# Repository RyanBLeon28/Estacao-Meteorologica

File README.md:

<h1>Estação Meteorológica Microcontrolada</h1>

<div align="center">
    
</div>

As estações meteorológicas são equipamentos utilizados para monitoramento e registro de condições climáticas por meio de sensores que analisam parâmetros atmosféricos como temperatura, umidade, pressão, velocidade e direção do vento. Neste projeto, os sensores estão conectados a um microcontrolador responsável por realizar a leitura dos dados. Esses dados são enviados automaticamente por protocolo LoRa(Long Range) para um servidor remoto (Datalogger), que realiza o armazenamento e processamento das informações.

O sistema foi projetado para operar continuamente e com baixo consumo de energia, sendo ideal para aplicações em ambientes externos. A visualização dos dados é feita por meio de dashboards acessíveis via navegador, possibilitando o acompanhamento em tempo real das variáveis monitoradas.

<h2>Tecnologias Utilizadas</h2>

<ul>
    <li><strong>MQTT (Eclipse Mosquitto):</strong> protocolo leve de comunicação utilizado para transmitir os dados dos sensores de forma eficiente e confiável.</li>
    <li><strong>Node.js:</strong> ambiente de execução utilizado no backend para processar as mensagens recebidas e integrá-las aos demais componentes do sistema.</li>
    <li><strong>Node-RED:</strong> ferramenta baseada em fluxo que facilita a criação de integrações entre os dados do MQTT e os bancos de dados utilizados.</li>
    <li><strong>InfluxDB:</strong> banco de dados especializado em séries temporais, utilizado para armazenar os dados dos sensores com alta performance.</li>
    <li><strong>Grafana:</strong> plataforma para visualização de dados que permite criar dashboards interativos e intuitivos para o acompanhamento das variáveis climáticas.</li>
</ul>

<h2>Detalhamento do projeto</h2>

<p>Para mais detalhes sobre o desenvolvimento da estação, incluindo a calibração de sensores como o anemômetro e a integração dos dados, consulte o <a href="Estação_Meteorológica_Microcontrolada.pdf" target="_blank">Relatório Descritivo do Projeto</a>.</p>

<h2>Referências</h2>

<p>
NODE.JS. Node.js. Disponível em: <a href="https://nodejs.org/en">https://nodejs.org/en</a>. Acesso em: 19 maio 2023.
</p>
<p>
MOSQUITTO. Mosquitto. Disponível em: <a href="https://mosquitto.org/">https://mosquitto.org/</a>. Acesso em: 19 maio 2023.
</p>
<p>
NODE-RED. Node-RED. Disponível em: <a href="https://nodered.org/">https://nodered.org/</a>. Acesso em: 19 maio 2023.
</p>
<p>
INFLUXDATA. Documentation. Disponível em: <a href="https://docs.influxdata.com/">https://docs.influxdata.com/</a>. Acesso em: 19 maio 2023.
</p>
<p>
GRAFANA LABS. Grafana. Disponível em: <a href="https://grafana.com/">https://grafana.com/</a>. Acesso em: 19 maio 2023.
</p>

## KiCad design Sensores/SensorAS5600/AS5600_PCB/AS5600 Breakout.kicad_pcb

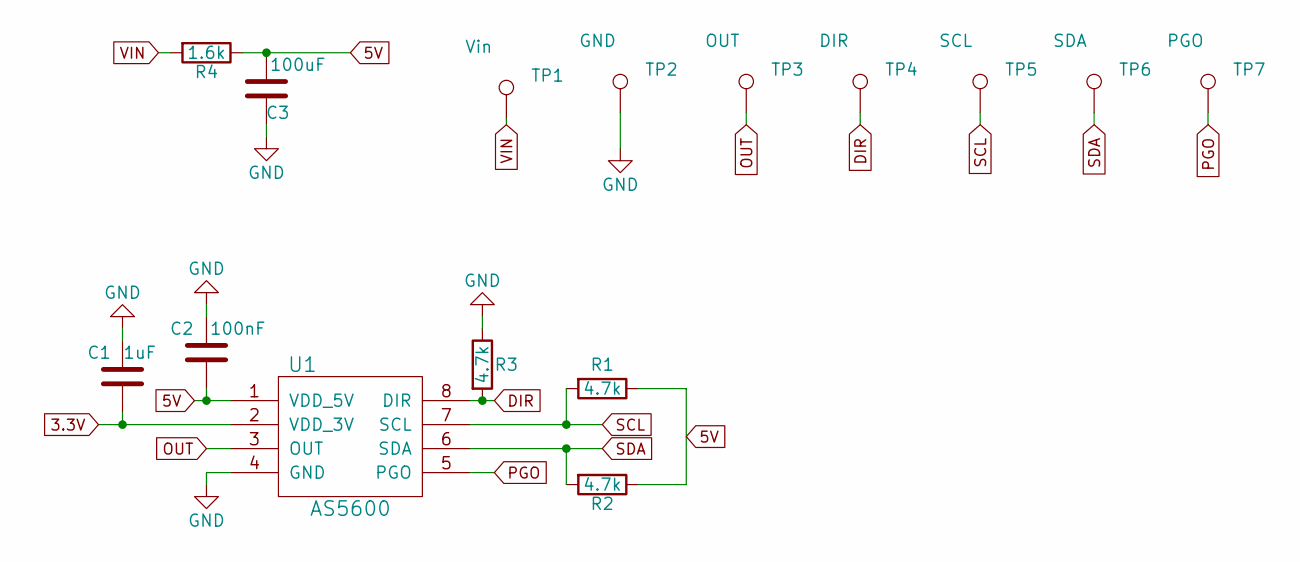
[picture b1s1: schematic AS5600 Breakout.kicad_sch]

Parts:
C1: 1uF; C_0805
C2: 100nF; C_0805
C3: 100uF; C_1210
R1, R2, R3: 4.7k; R_0805
R4: 1.6k; R_0805
TP1: Vin; TestPoint_Pad_D1.0mm
TP2: GND; TestPoint_Pad_D1.0mm
TP3: OUT; TestPoint_Pad_D1.0mm
TP4: DIR; TestPoint_Pad_D1.0mm
TP5: SCL; TestPoint_Pad_D1.0mm
TP6: SDA; TestPoint_Pad_D1.0mm
TP7: PGO; TestPoint_Pad_D1.0mm
U1: AS5600; SOIC-8-N; Manufacturer Part Number AS5600-ASOM

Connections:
3.3V: C1.2, U1.2 (VDD_3V)
5V: C2.1, C3.2, R1.1, R2.1, R4.1, U1.1 (VDD_5V)
DIR: R3.2, TP4.1, U1.8 (DIR)
GND: C1.1, C2.2, C3.1, R3.1, TP2.1, U1.4 (GND)
OUT: TP3.1, U1.3 (OUT)
PGO: TP7.1, U1.5 (PGO)
SCL: R1.2, TP5.1, U1.7 (SCL)
SDA: R2.2, TP6.1, U1.6 (SDA)
VIN: R4.2, TP1.1

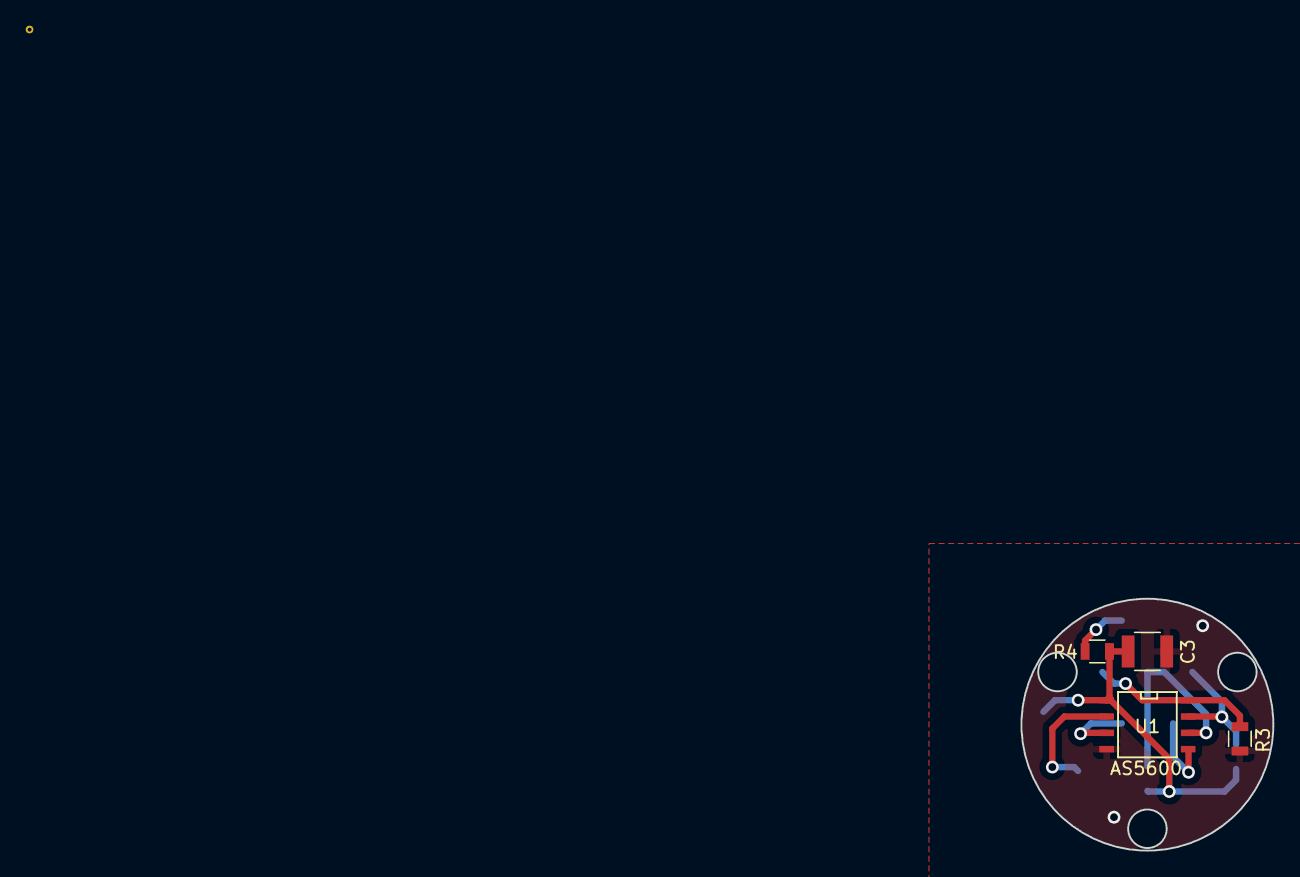
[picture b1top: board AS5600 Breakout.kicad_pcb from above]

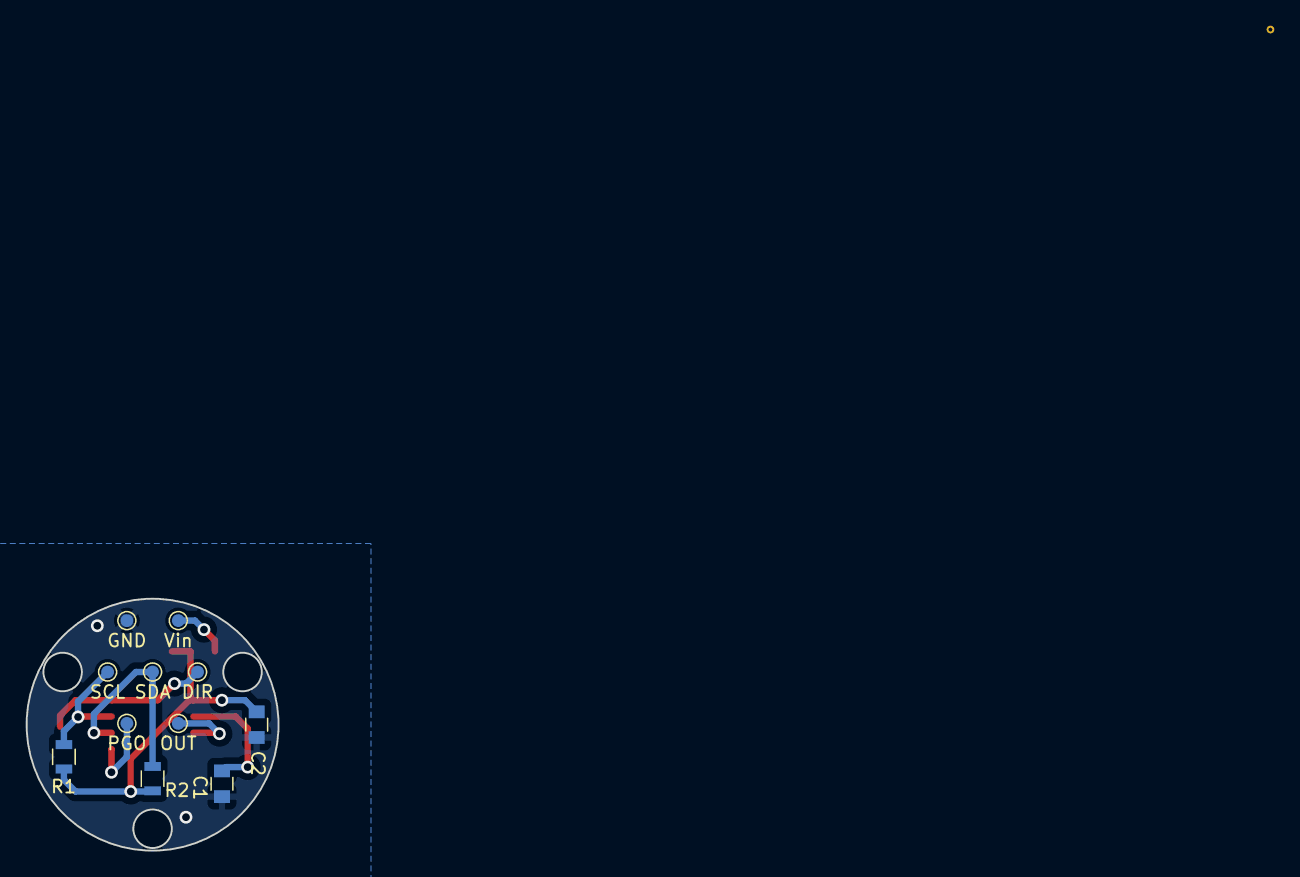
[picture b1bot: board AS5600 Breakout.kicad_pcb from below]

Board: 2 copper layers, 19.6 x 19.6 mm, 15 parts (11 on the bottom side), 9 nets.

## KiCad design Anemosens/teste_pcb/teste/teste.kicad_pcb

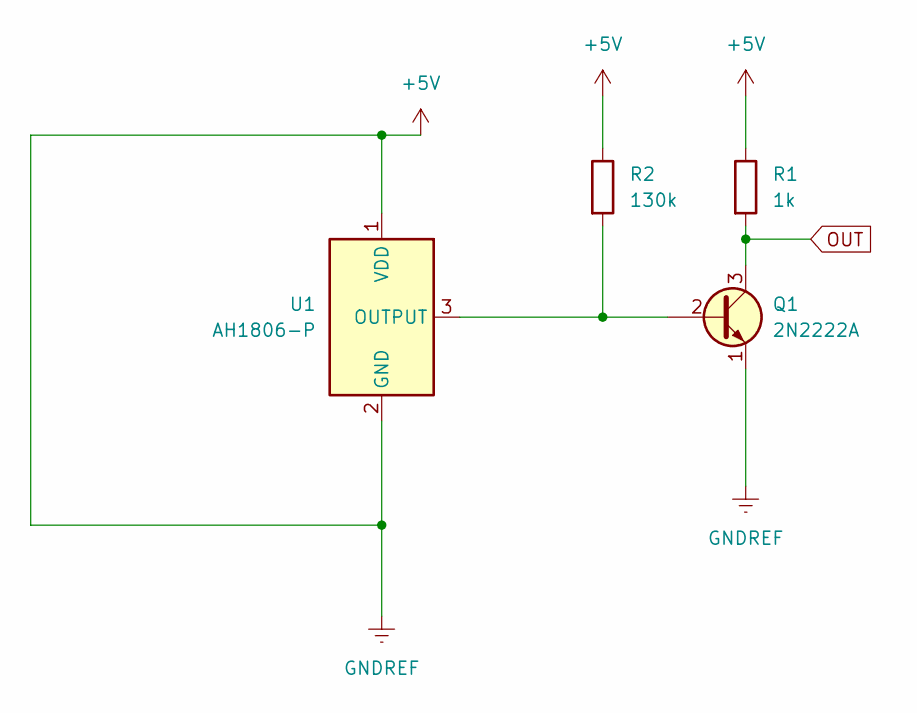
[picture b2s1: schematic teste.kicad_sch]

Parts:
Q1: 2N2222A; TO-92_Inline_Horizontal2
R1: 1k; R_Axial_DIN0204_L3.6mm_D1.6mm_P7.62mm_Horizontal
R2: 130k; R_Axial_DIN0204_L3.6mm_D1.6mm_P7.62mm_Horizontal
U1: AH1806-P; TO-92S

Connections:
+5V: Q1.1 (E), R1.1, R2.1, U1.1 (VDD), U1.2 (GND)
unnamed: Q1.2 (B), R2.2, U1.3 (OUTPUT)
OUT: Q1.3 (C), R1.2

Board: 2 copper layers, 4 parts (0 on the bottom side), 3 nets, no tracks yet.

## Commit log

2023-07-10 Anemosens
2023-09-24 Acertando os arquivos
2023-09-25 exclusao de sensorBMP280
2023-09-25 Done
2023-09-25 remocao
2023-09-25 removing
2023-09-25 changed de fotos name
2023-09-25 teste fork pasta
2023-09-25 changed the folder name
2023-09-25 changed the folder's name
2023-09-25 chaged the folder's name
2023-09-25 mudei o nome da pasta
2023-09-25 atualizei
2023-09-25 atual
2023-09-25 mudancas
2023-09-25 testando
2023-09-25 mudanca
2023-09-25 exclui
2024-03-04 organizando
2024-03-04 organizacao
2024-03-04 pastas
2024-03-12 anemometro
2024-03-21 anemometro3D
2024-03-21 codigoGeral
2024-04-09 lora communication and sending to mqtt protocol
2024-04-23 AS5600 sensor added
2024-05-04 readme
2024-05-05 readme e fotos
2024-05-05 ajuste
2024-05-13 Organização
